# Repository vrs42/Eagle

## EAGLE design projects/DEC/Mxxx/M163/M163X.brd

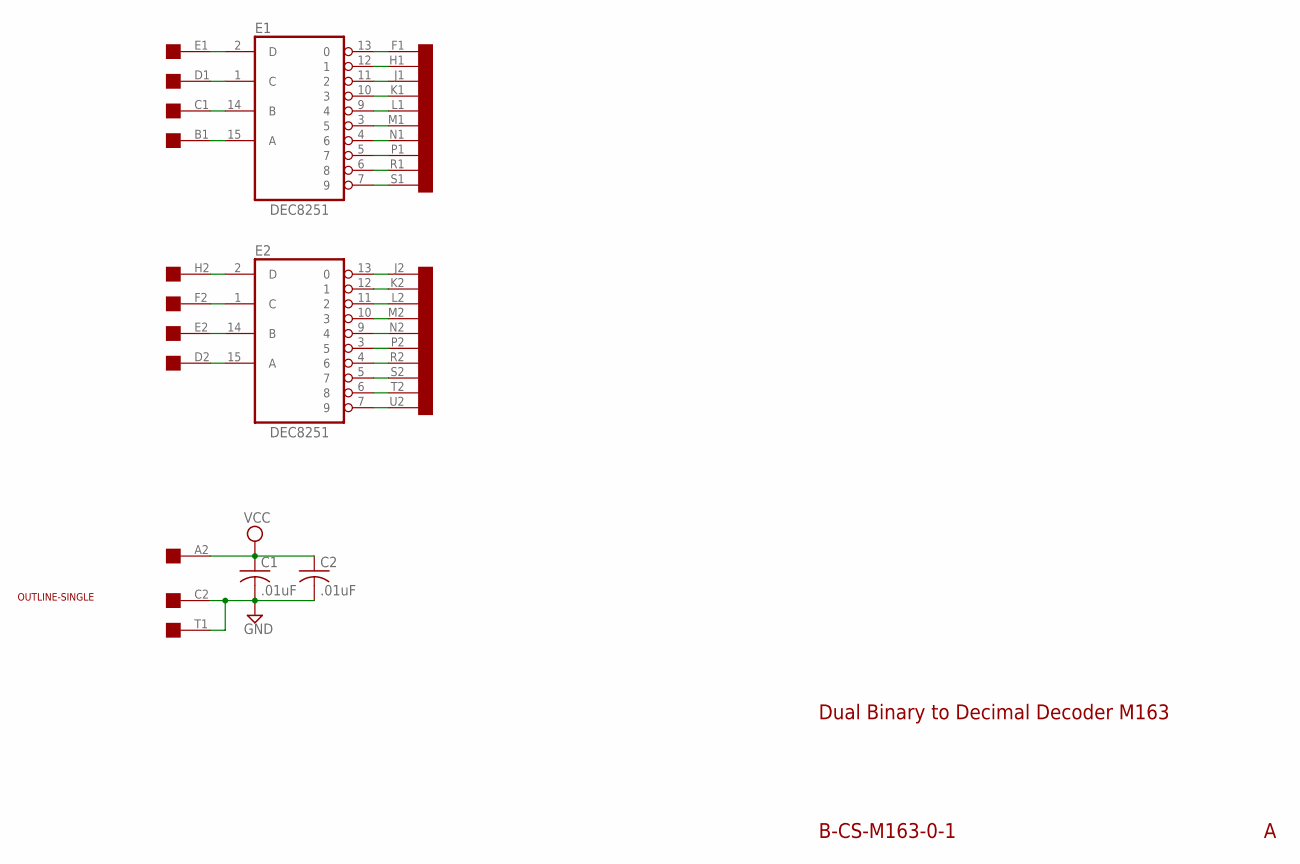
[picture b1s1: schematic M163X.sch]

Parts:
C1, C2: .01uF; C050-025X075
E1, E2: DEC8251; DIL16
U$1: OUTLINE-SINGLE; SINGLE
U$2: SINGLE; EDGE-CON2

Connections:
GND: C1.2, C2.2, E1.8 (GND), E2.8 (GND), U$2.C2, U$2.T1
unnamed: E1.15 (A), U$2.B1
unnamed: E1.14 (B), U$2.C1
unnamed: E1.1 (C), U$2.D1
unnamed: E1.2 (D), U$2.E1
unnamed: E1.13 (0), U$2.F1
unnamed: E1.12 (1), U$2.H1
unnamed: E1.11 (2), U$2.J1
unnamed: E1.10 (3), U$2.K1
unnamed: E1.3 (5), U$2.M1
unnamed: E1.9 (4), U$2.L1
unnamed: E1.4 (6), U$2.N1
unnamed: E1.5 (7), U$2.P1
unnamed: E1.6 (8), U$2.R1
unnamed: E1.7 (9), U$2.S1
unnamed: E2.2 (D), U$2.H2
unnamed: E2.1 (C), U$2.F2
unnamed: E2.15 (A), U$2.D2
unnamed: E2.14 (B), U$2.E2
unnamed: E2.11 (2), U$2.L2
unnamed: E2.10 (3), U$2.M2
unnamed: E2.9 (4), U$2.N2
unnamed: E2.3 (5), U$2.P2
unnamed: E2.4 (6), U$2.R2
unnamed: E2.5 (7), U$2.S2
unnamed: E2.6 (8), U$2.T2
unnamed: E2.12 (1), U$2.K2
unnamed: E2.13 (0), U$2.J2
unnamed: E2.7 (9), U$2.U2
VCC: C1.1, C2.1, E1.16 (VCC), E2.16 (VCC), U$2.A2

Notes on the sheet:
B-CS-M163-0-1
Dual Binary to Decimal Decoder M163

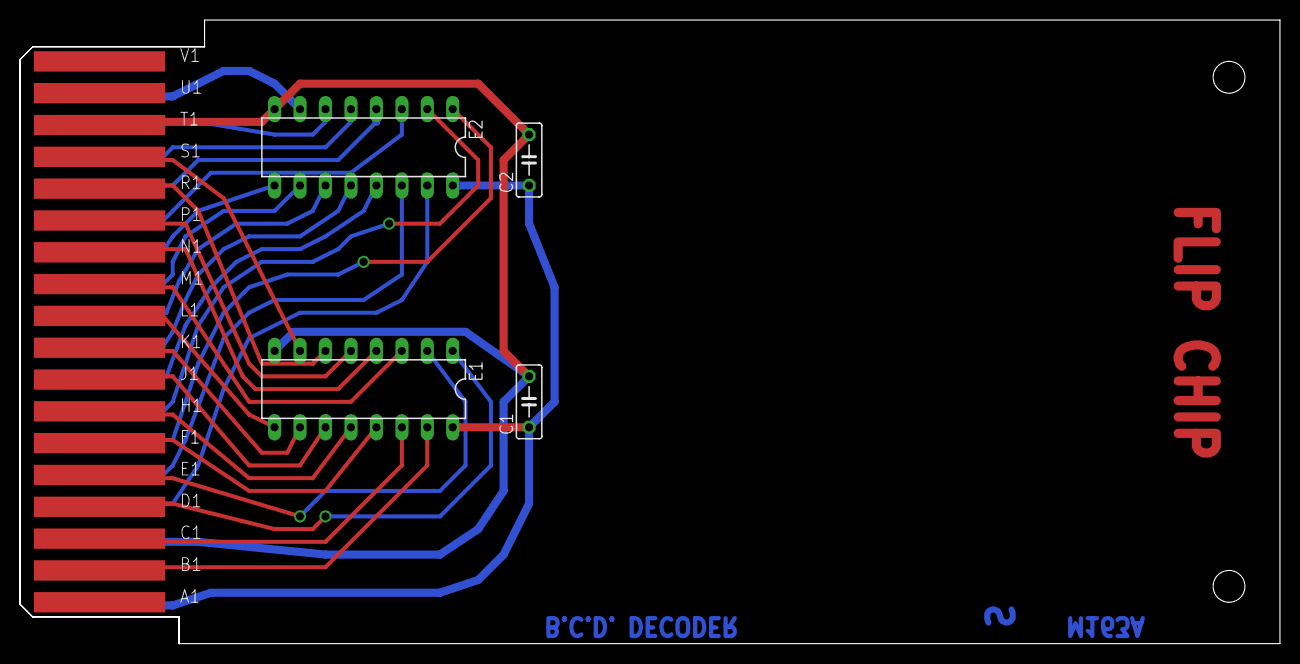
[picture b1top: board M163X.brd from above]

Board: 2 copper layers, 125.7 x 62.2 mm, 6 parts (0 on the bottom side), 30 nets.

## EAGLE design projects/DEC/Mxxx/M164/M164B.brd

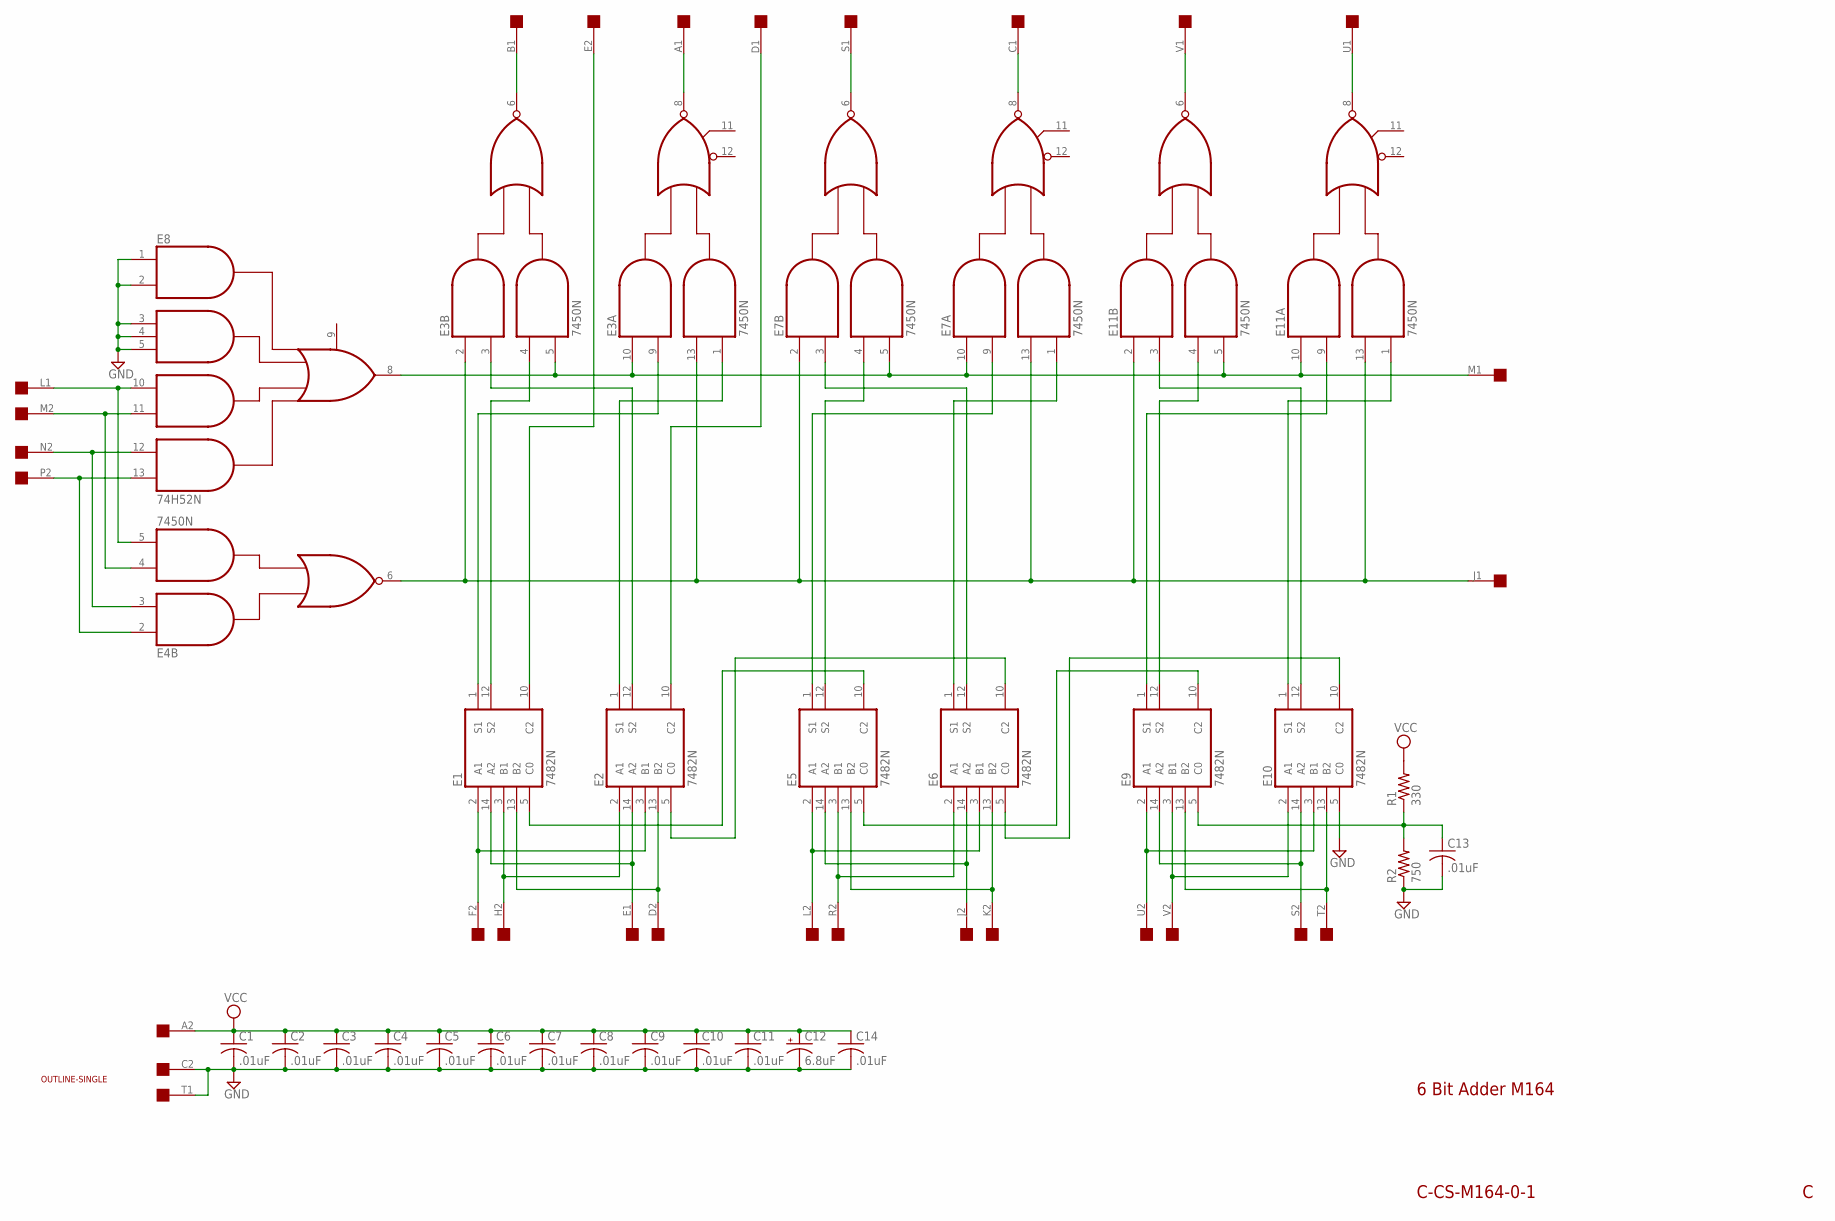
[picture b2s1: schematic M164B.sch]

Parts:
C1, C2, C3, C4, C5, C6, C7, C8, C9, C10, C11, C13, C14: .01uF; C050-025X075
C12: 6.8uF; E12-8
E1, E2, E5, E6, E9, E10: 7482N; DIL14
E3, E4, E7, E11: 7450N; DIL14
E8: 74H52N; DIL14
R1: 330; 0207/10
R2: 750; 0207/10
U$1: SINGLE; EDGE-CON2
U$2: OUTLINE-SINGLE; SINGLE

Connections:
GND: C1.2, C2.2, C3.2, C4.2, C5.2, C6.2, C7.2, C8.2, C9.2, C10.2, C11.2, C12.-, C13.2, C14.2, E1.11 (GND), E2.11 (GND), E3.7 (GND), E4.7 (GND), E5.11 (GND), E6.11 (GND), E7.7 (GND), E8.1 (I1), E8.2 (I2), E8.3 (I3), E8.4 (I4), E8.5 (I5), E8.7 (GND), E9.11 (GND), E10.5 (C0), E10.11 (GND), E11.7 (GND), R2.1, U$1.C2, U$1.T1
unnamed: E4.3 (I2), E8.12 (I12), U$1.N2
unnamed: E4.5 (I4), E8.10 (I10), U$1.L1
unnamed: E4.4 (I3), E8.11 (I11), U$1.M2
unnamed: E4.2 (I1), E8.13 (I13), U$1.P2
unnamed: E1.2 (A1), E2.3 (B1), U$1.F2
unnamed: E1.3 (B1), E2.2 (A1), U$1.H2
unnamed: E1.13 (B2), E2.13 (B2), U$1.D2
unnamed: E1.14 (A2), E2.14 (A2), U$1.E1
unnamed: E3.2 (I1), E3.13 (I3), E4.6 (O), E7.2 (I1), E7.13 (I3), E11.2 (I1), E11.13 (I3), U$1.J1
unnamed: E3.5 (I4), E3.10 (I1), E7.5 (I4), E7.10 (I1), E8.8 (O8), E11.5 (I4), E11.10 (I1), U$1.M1
unnamed: E2.12 (S2), E3.3 (I2)
unnamed: E1.12 (S2), E3.4 (I3)
unnamed: E2.1 (S1), E3.1 (I4)
unnamed: E1.1 (S1), E3.9 (I2)
unnamed: E1.10 (C2), U$1.E2
unnamed: E2.10 (C2), U$1.D1
unnamed: E3.8 (O), U$1.A1
unnamed: E3.6 (O), U$1.B1
unnamed: E1.5 (C0), E5.10 (C2)
unnamed: E2.5 (C0), E6.10 (C2)
unnamed: E5.2 (A1), E6.3 (B1), U$1.L2
unnamed: E5.3 (B1), E6.2 (A1), U$1.R2
unnamed: E5.13 (B2), E6.13 (B2), U$1.K2
unnamed: E5.14 (A2), E6.14 (A2), U$1.J2
unnamed: C13.1, E9.5 (C0), R1.1, R2.2
unnamed: E9.3 (B1), E10.2 (A1), U$1.V2
unnamed: E6.12 (S2), E7.3 (I2)
unnamed: E5.12 (S2), E7.4 (I3)
unnamed: E6.1 (S1), E7.1 (I4)
unnamed: E5.1 (S1), E7.9 (I2)
unnamed: E7.8 (O), U$1.C1
unnamed: E7.6 (O), U$1.S1
unnamed: E6.5 (C0), E10.10 (C2)
unnamed: E9.2 (A1), E10.3 (B1), U$1.U2
unnamed: E9.13 (B2), E10.13 (B2), U$1.T2
unnamed: E9.14 (A2), E10.14 (A2), U$1.S2
unnamed: E10.12 (S2), E11.3 (I2)
unnamed: E9.12 (S2), E11.4 (I3)
unnamed: E10.1 (S1), E11.1 (I4)
unnamed: E9.1 (S1), E11.9 (I2)
unnamed: E5.5 (C0), E9.10 (C2)
unnamed: E11.8 (O), U$1.U1
unnamed: E11.6 (O), U$1.V1
VCC: C1.1, C2.1, C3.1, C4.1, C5.1, C6.1, C7.1, C8.1, C9.1, C10.1, C11.1, C12.+, C14.1, E1.4 (VCC), E2.4 (VCC), E3.14 (VCC), E4.14 (VCC), E5.4 (VCC), E6.4 (VCC), E7.14 (VCC), E8.14 (VCC), E9.4 (VCC), E10.4 (VCC), E11.14 (VCC), R1.2, U$1.A2

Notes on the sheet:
6 Bit Adder M164
C-CS-M164-0-1

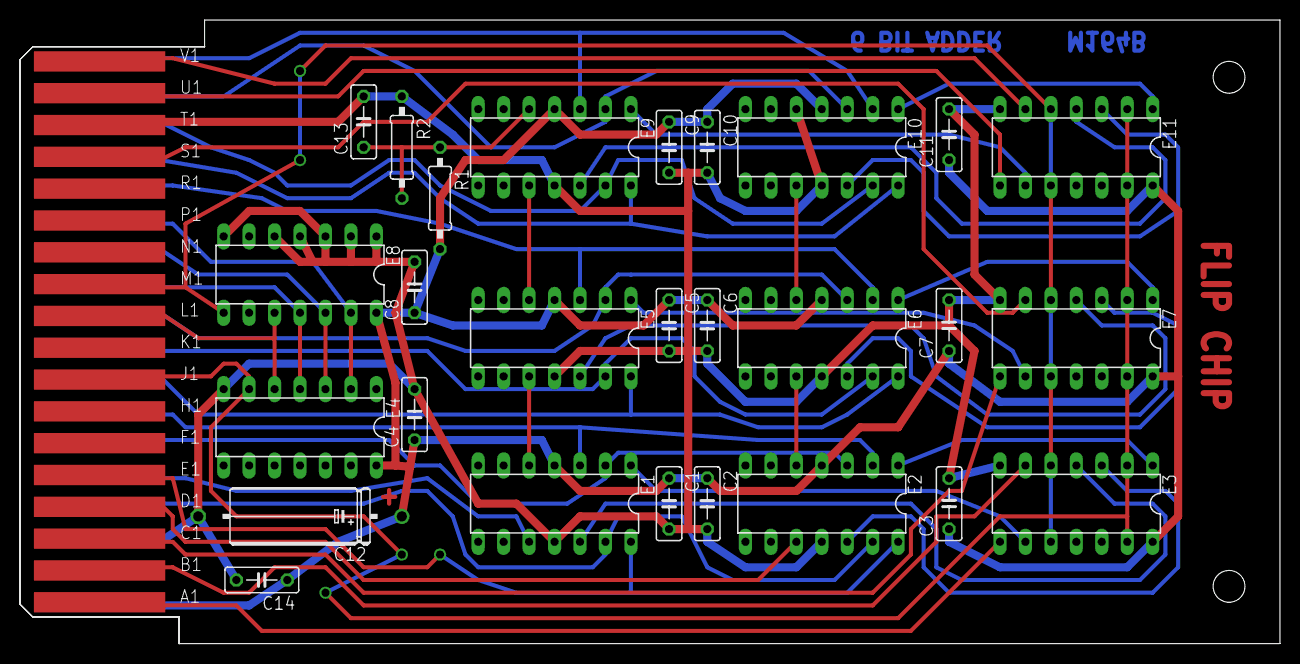
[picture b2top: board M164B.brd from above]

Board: 2 copper layers, 125.7 x 62.2 mm, 29 parts (0 on the bottom side), 45 nets.

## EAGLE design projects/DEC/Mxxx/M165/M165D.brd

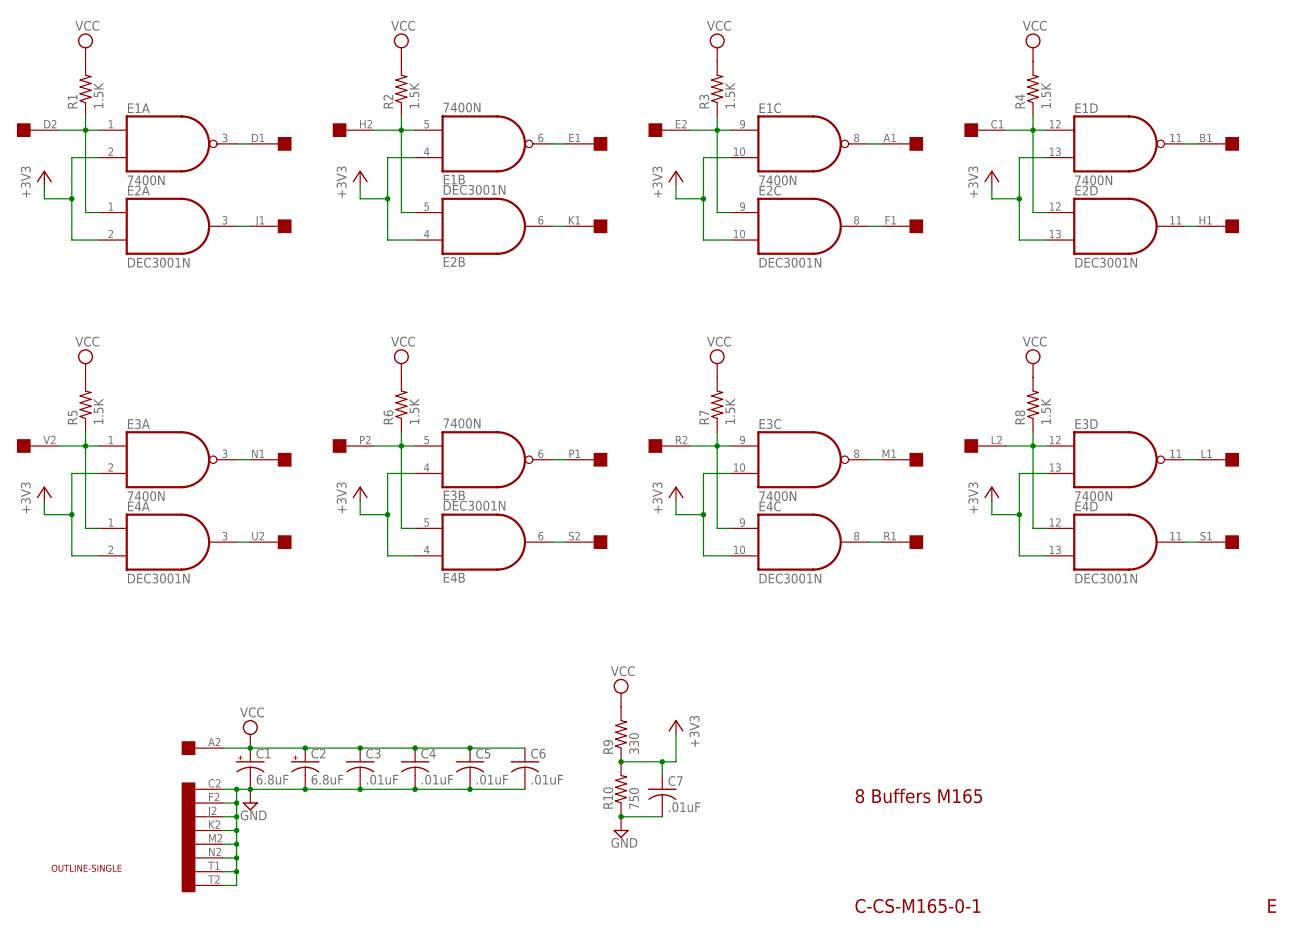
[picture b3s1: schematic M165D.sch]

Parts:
C1, C2: 6.8uF; E25-9
C3, C4, C5, C6, C7: .01uF; C050-025X075
E1, E3: 7400N; DIL14
E2, E4: DEC3001N; DIL14
R1, R2, R3, R4, R5, R6, R7, R8: 1.5K; 0207/10
R9: 330; 0207/10
R10: 750; 0207/10
U$1: SINGLE; EDGE-CON2
U$2: OUTLINE-SINGLE; SINGLE

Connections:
+3V3: C7.1, E1.2 (I1), E1.4 (I0), E1.10 (I1), E1.13 (I1), E2.2 (I1), E2.4 (I0), E2.10 (I1), E2.13 (I1), E3.2 (I1), E3.4 (I0), E3.10 (I1), E3.13 (I1), E4.2 (I1), E4.4 (I0), E4.10 (I1), E4.13 (I1), R9.1, R10.2
GND: C1.-, C2.-, C3.2, C4.2, C5.2, C6.2, C7.2, E1.7 (GND), E2.7 (GND), E3.7 (GND), E4.7 (GND), R10.1, U$1.C2, U$1.F2, U$1.J2, U$1.K2, U$1.M2, U$1.N2, U$1.T1, U$1.T2
unnamed: E1.1 (I0), E2.1 (I0), R1.1, U$1.D2
unnamed: E1.5 (I1), E2.5 (I1), R2.1, U$1.H2
unnamed: E2.3 (O), U$1.J1
unnamed: E1.3 (O), U$1.D1
unnamed: E2.6 (O), U$1.K1
unnamed: E1.6 (O), U$1.E1
unnamed: E1.9 (I0), E2.9 (I0), R3.1, U$1.E2
unnamed: E2.8 (O), U$1.F1
unnamed: E1.8 (O), U$1.A1
unnamed: E1.12 (I0), E2.12 (I0), R4.1, U$1.C1
unnamed: E2.11 (O), U$1.H1
unnamed: E1.11 (O), U$1.B1
unnamed: E3.1 (I0), E4.1 (I0), R5.1, U$1.V2
unnamed: E4.3 (O), U$1.U2
unnamed: E3.3 (O), U$1.N1
unnamed: E3.5 (I1), E4.5 (I1), R6.1, U$1.P2
unnamed: E4.6 (O), U$1.S2
unnamed: E3.6 (O), U$1.P1
unnamed: E3.9 (I0), E4.9 (I0), R7.1, U$1.R2
unnamed: E4.8 (O), U$1.R1
unnamed: E3.8 (O), U$1.M1
unnamed: E3.12 (I0), E4.12 (I0), R8.1, U$1.L2
unnamed: E4.11 (O), U$1.S1
unnamed: E3.11 (O), U$1.L1
VCC: C1.+, C2.+, C3.1, C4.1, C5.1, C6.1, E1.14 (VCC), E2.14 (VCC), E3.14 (VCC), E4.14 (VCC), R1.2, R2.2, R3.2, R4.2, R5.2, R6.2, R7.2, R8.2, R9.2, U$1.A2

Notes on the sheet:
8 Buffers M165
C-CS-M165-0-1

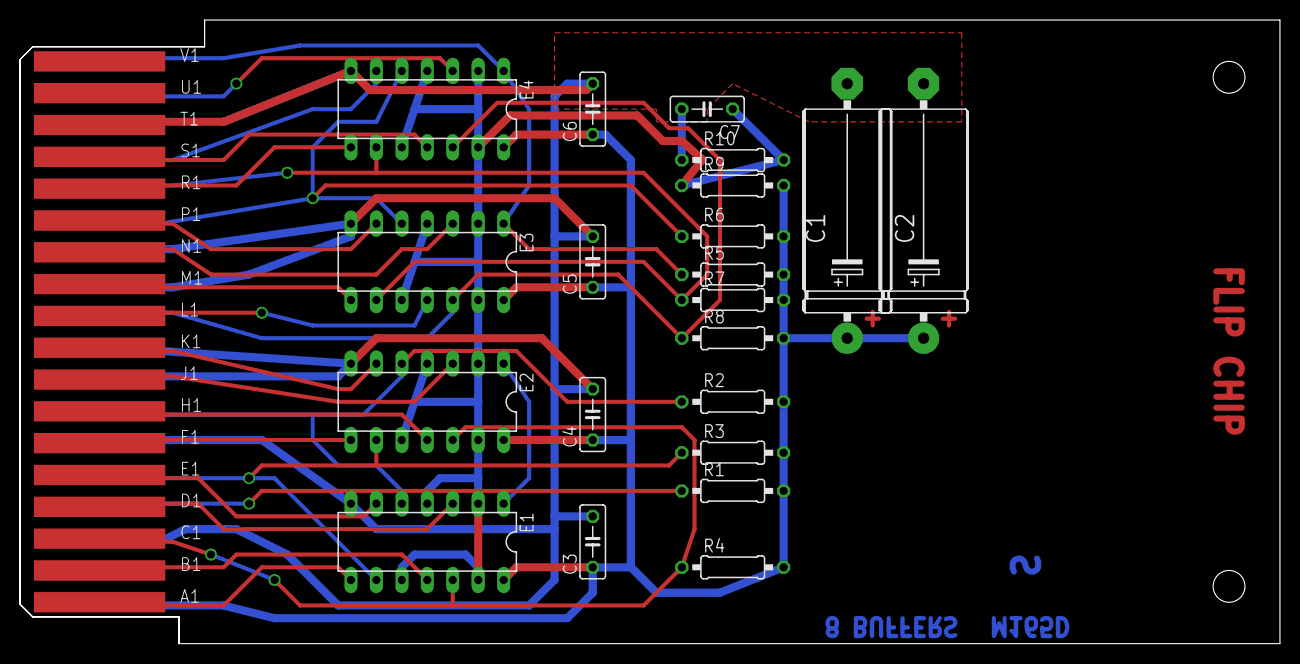
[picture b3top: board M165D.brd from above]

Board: 2 copper layers, 125.7 x 62.2 mm, 23 parts (0 on the bottom side), 27 nets.

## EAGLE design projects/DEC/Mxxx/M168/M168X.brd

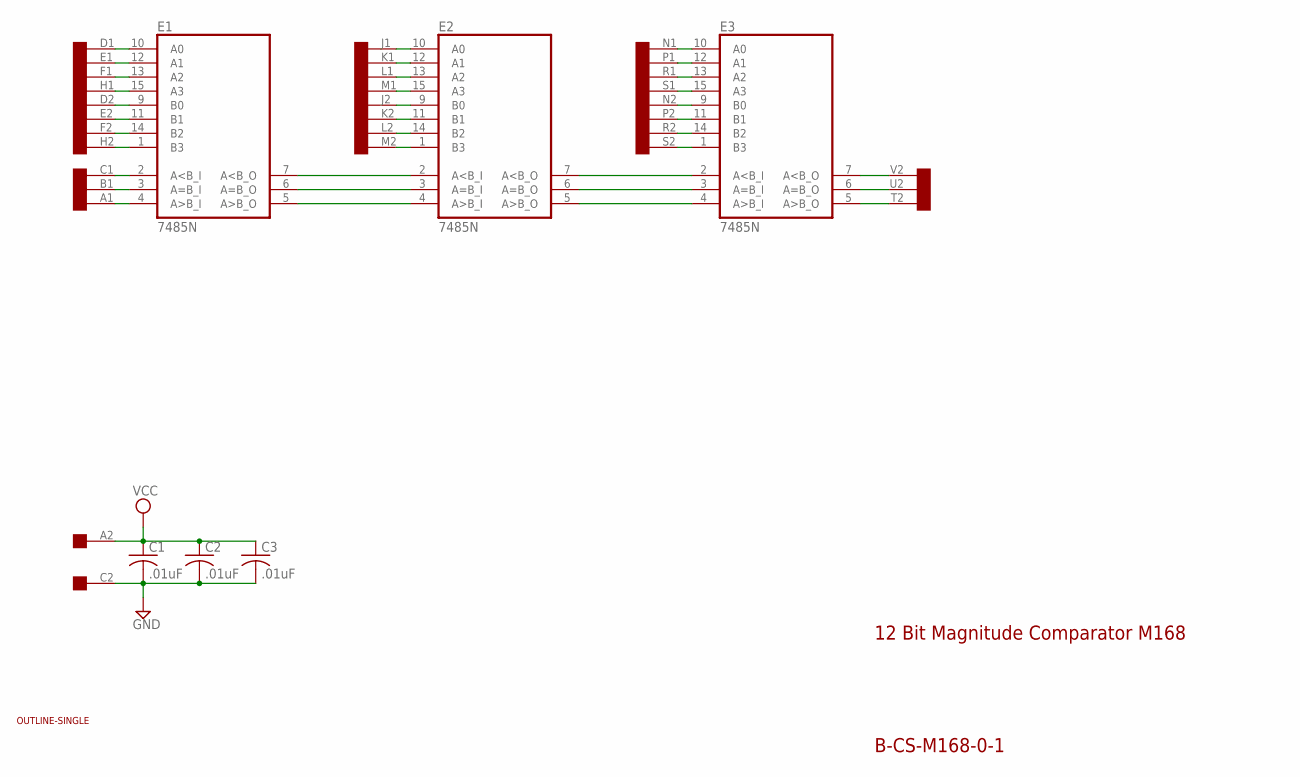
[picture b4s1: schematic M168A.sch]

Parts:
C1, C2, C3: .01uF; C050-025X075
E1, E2, E3: 7485N; DIL16
U$1: SINGLE; EDGE-CON2
U$2: OUTLINE-SINGLE; SINGLE

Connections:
A1: E1.4 (A>B_I), U$1.A1
B1: E1.3 (A=B_I), U$1.B1
C1: E1.2 (A<B_I), U$1.C1
D1: E1.10 (A0), U$1.D1
D2: E1.9 (B0), U$1.D2
E1: E1.12 (A1), U$1.E1
E2: E1.11 (B1), U$1.E2
F1: E1.13 (A2), U$1.F1
F2: E1.14 (B2), U$1.F2
GND: C1.2, C2.2, C3.2, E1.8 (GND), E2.8 (GND), E3.8 (GND), U$1.C2
H1: E1.15 (A3), U$1.H1
H2: E1.1 (B3), U$1.H2
J1: E2.10 (A0), U$1.J1
J2: E2.9 (B0), U$1.J2
K1: E2.12 (A1), U$1.K1
K2: E2.11 (B1), U$1.K2
L1: E2.13 (A2), U$1.L1
L2: E2.14 (B2), U$1.L2
M1: E2.15 (A3), U$1.M1
M2: E2.1 (B3), U$1.M2
N1: E3.10 (A0), U$1.N1
N2: E3.9 (B0), U$1.N2
unnamed: E1.6 (A=B_O), E2.3 (A=B_I)
unnamed: E1.7 (A<B_O), E2.2 (A<B_I)
unnamed: E1.5 (A>B_O), E2.4 (A>B_I)
unnamed: E2.6 (A=B_O), E3.3 (A=B_I)
unnamed: E2.7 (A<B_O), E3.2 (A<B_I)
unnamed: E2.5 (A>B_O), E3.4 (A>B_I)
P1: E3.12 (A1), U$1.P1
P2: E3.11 (B1), U$1.P2
R1: E3.13 (A2), U$1.R1
R2: E3.14 (B2), U$1.R2
S1: E3.15 (A3), U$1.S1
S2: E3.1 (B3), U$1.S2
T2: E3.5 (A>B_O), U$1.T2
U2: E3.6 (A=B_O), U$1.U2
V2: E3.7 (A<B_O), U$1.V2
VCC: C1.1, C2.1, C3.1, E1.16 (VCC), E2.16 (VCC), E3.16 (VCC), U$1.A2

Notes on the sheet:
12 Bit Magnitude Comparator M168
B-CS-M168-0-1

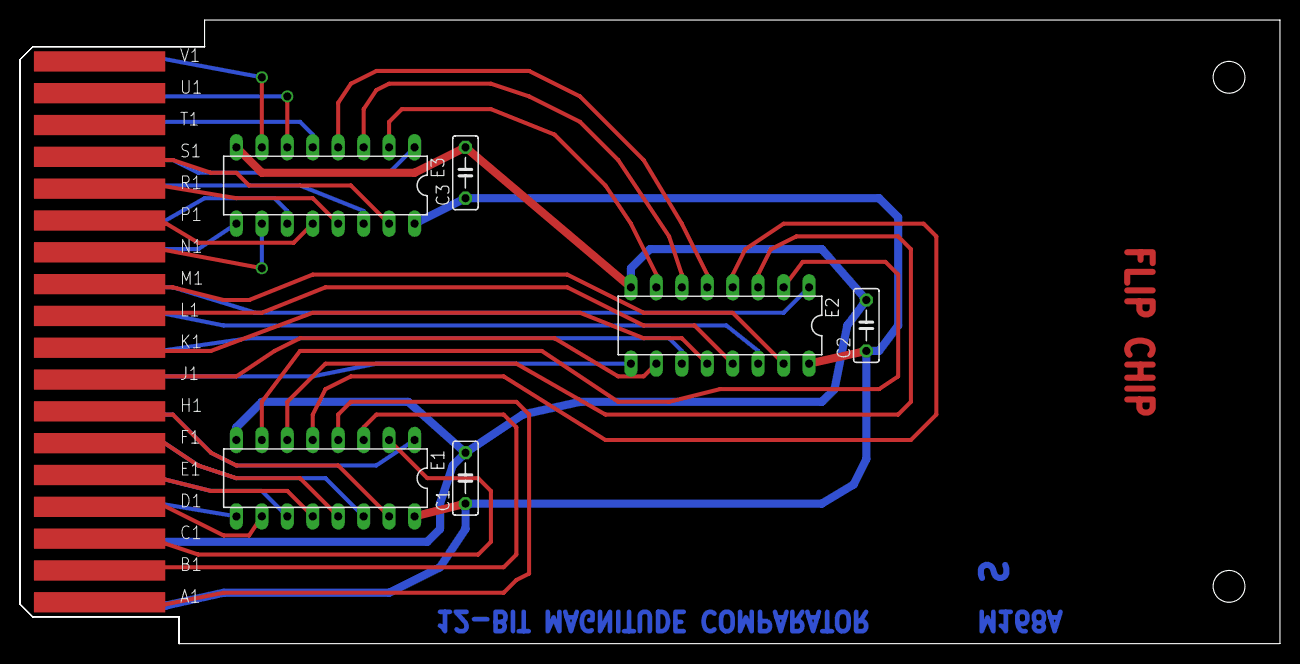
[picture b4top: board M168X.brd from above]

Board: 2 copper layers, 125.7 x 62.2 mm, 8 parts (0 on the bottom side), 38 nets.

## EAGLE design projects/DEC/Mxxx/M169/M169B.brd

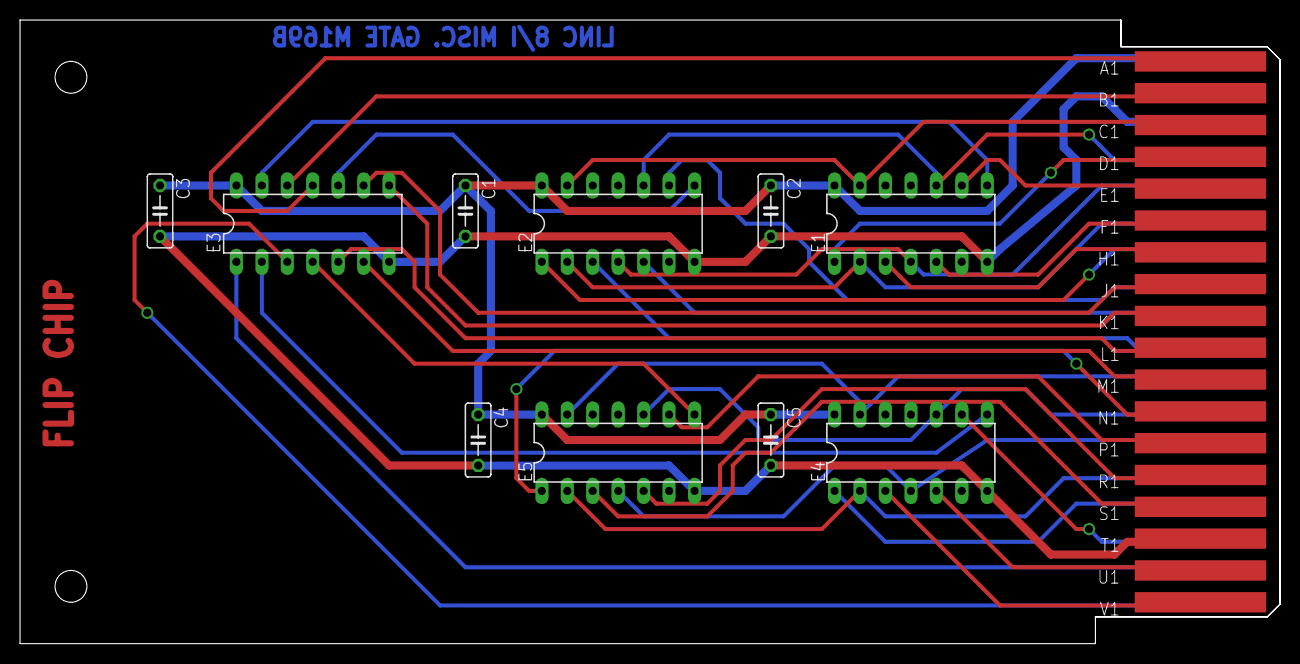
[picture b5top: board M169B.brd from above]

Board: 2 copper layers, 125.7 x 62.2 mm, 13 parts (0 on the bottom side), 38 nets.

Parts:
C1, C2, C3, C4, C5: .01uf; C050-025X075
E1, E2, E4, E5: 7453N; DIL14
E3: 7400N; DIL14
U$1: OUTLINE-SINGLE; SINGLE
U$2: EDGE-CON2
U$3: FLIPCHIP

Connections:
GND: C1.2, C2.2, C3.2, C4.2, C5.2, E1.7, E2.7, E3.7, E4.7, E5.7, U$2.C2, U$2.T1
unnamed: E1.8, E3.13
unnamed: E3.11, U$2.A1
unnamed: E1.13, E2.13, U$2.C1
unnamed: E1.10, E2.10, U$2.D2
unnamed: E1.4, E2.4, U$2.E2
unnamed: E1.2, E2.2, U$2.F2
unnamed: E2.8, E3.10
unnamed: E3.8, U$2.K1
unnamed: E2.9, U$2.J2
unnamed: E1.5, U$2.F1
unnamed: E1.1, U$2.D1
unnamed: E1.3, U$2.H1
unnamed: E1.9, U$2.E1
unnamed: E3.12, U$2.B1
unnamed: E2.5, U$2.K2
unnamed: E2.1, U$2.H2
unnamed: E2.3, U$2.L2
unnamed: E4.13, E5.13, U$2.M2
unnamed: E4.10, E5.10, U$2.N2
unnamed: E4.4, E5.4, U$2.P2
unnamed: E4.2, E5.2, U$2.R2
unnamed: E3.4, E5.8
unnamed: E3.2, E4.8
unnamed: E3.9, U$2.J1
unnamed: E4.9, U$2.T2
unnamed: E5.1, U$2.N1
unnamed: E5.5, U$2.R1
unnamed: E5.3, U$2.S1
unnamed: E5.9, U$2.P1
unnamed: E3.5, U$2.L1
unnamed: E4.5, U$2.U1
unnamed: E4.1, U$2.S2
unnamed: E4.3, U$2.V1
unnamed: E3.1, U$2.U2
unnamed: E3.6, U$2.M1
unnamed: E3.3, U$2.V2
VCC: C1.1, C2.1, C3.1, C4.1, C5.1, E1.14, E2.14, E3.14, E4.14, E5.14, U$2.A2

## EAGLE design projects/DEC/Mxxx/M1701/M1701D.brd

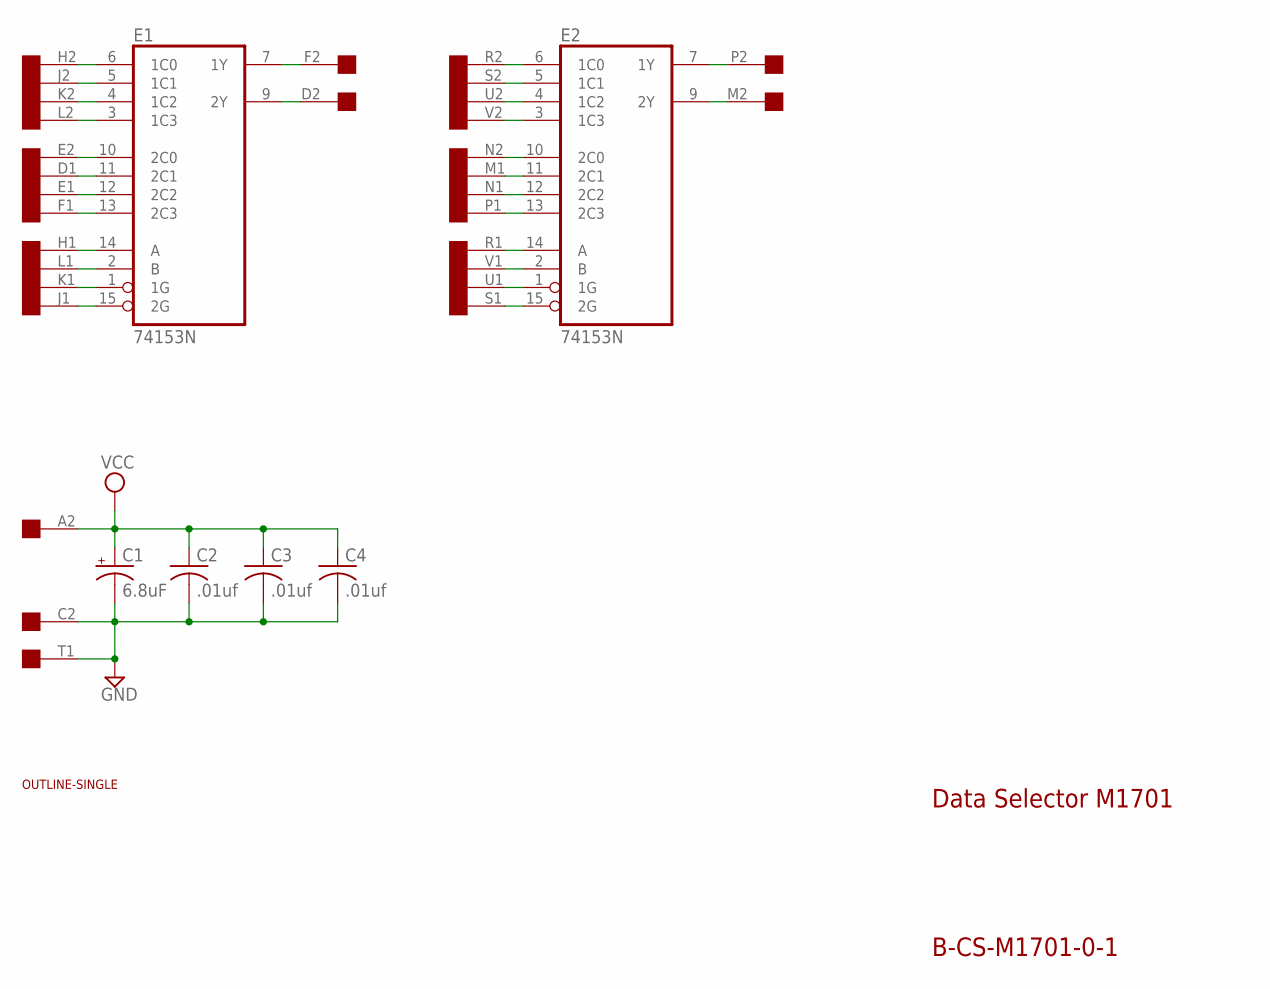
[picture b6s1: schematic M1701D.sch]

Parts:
C1: 6.8uF; E12-8
C2, C3, C4: .01uf; C050-025X075
E1, E2: 74153N; DIL16
U$1: OUTLINE-SINGLE; SINGLE
U$2: SINGLE; EDGE-CON2

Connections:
GND: C1.-, C2.2, C3.2, C4.2, E1.8 (GND), E2.8 (GND), U$2.C2, U$2.T1
unnamed: E1.6 (1C0), U$2.H2
unnamed: E1.5 (1C1), U$2.J2
unnamed: E1.4 (1C2), U$2.K2
unnamed: E1.3 (1C3), U$2.L2
unnamed: E1.10 (2C0), U$2.E2
unnamed: E1.11 (2C1), U$2.D1
unnamed: E1.12 (2C2), U$2.E1
unnamed: E1.13 (2C3), U$2.F1
unnamed: E1.1 (1G), U$2.K1
unnamed: E1.2 (B), U$2.L1
unnamed: E1.14 (A), U$2.H1
unnamed: E1.15 (2G), U$2.J1
unnamed: E1.9 (2Y), U$2.D2
unnamed: E1.7 (1Y), U$2.F2
unnamed: E2.6 (1C0), U$2.R2
unnamed: E2.5 (1C1), U$2.S2
unnamed: E2.4 (1C2), U$2.U2
unnamed: E2.3 (1C3), U$2.V2
unnamed: E2.1 (1G), U$2.U1
unnamed: E2.15 (2G), U$2.S1
unnamed: E2.2 (B), U$2.V1
unnamed: E2.10 (2C0), U$2.N2
unnamed: E2.11 (2C1), U$2.M1
unnamed: E2.12 (2C2), U$2.N1
unnamed: E2.13 (2C3), U$2.P1
unnamed: E2.14 (A), U$2.R1
unnamed: E2.7 (1Y), U$2.P2
unnamed: E2.9 (2Y), U$2.M2
VCC: C1.+, C2.1, C3.1, C4.1, E1.16 (VCC), E2.16 (VCC), U$2.A2

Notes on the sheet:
Data Selector M1701
B-CS-M1701-0-1

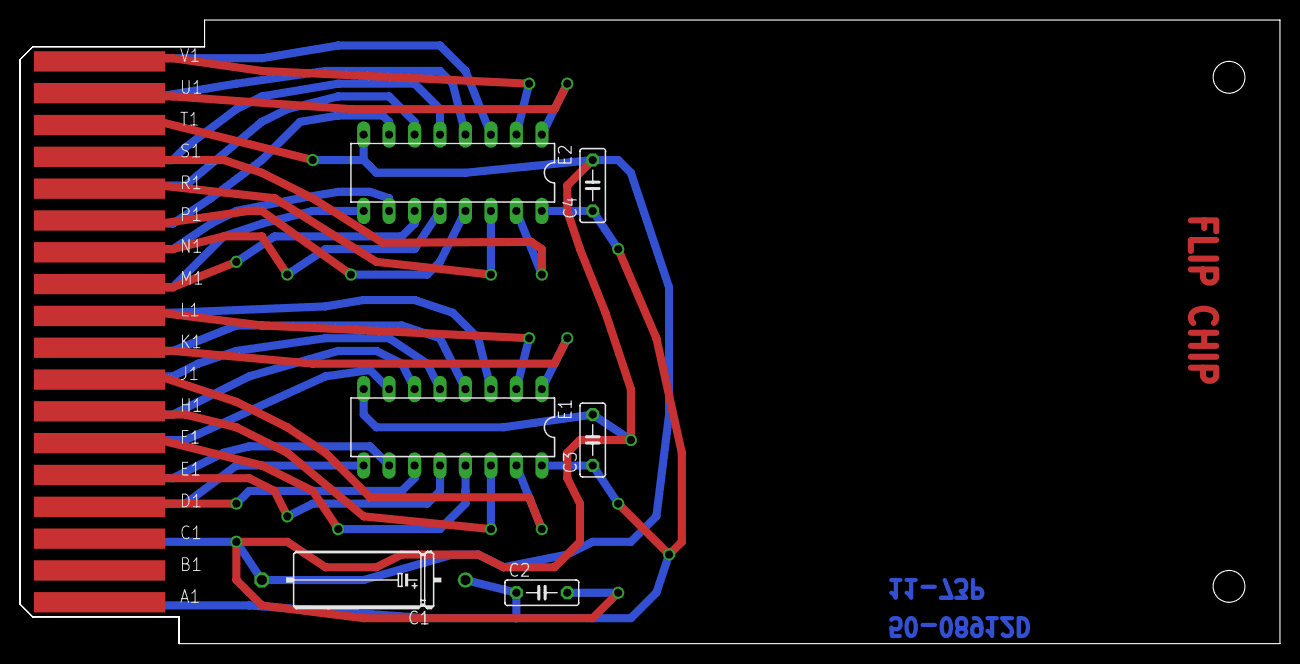
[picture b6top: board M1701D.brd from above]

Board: 2 copper layers, 125.7 x 62.2 mm, 8 parts (0 on the bottom side), 30 nets.

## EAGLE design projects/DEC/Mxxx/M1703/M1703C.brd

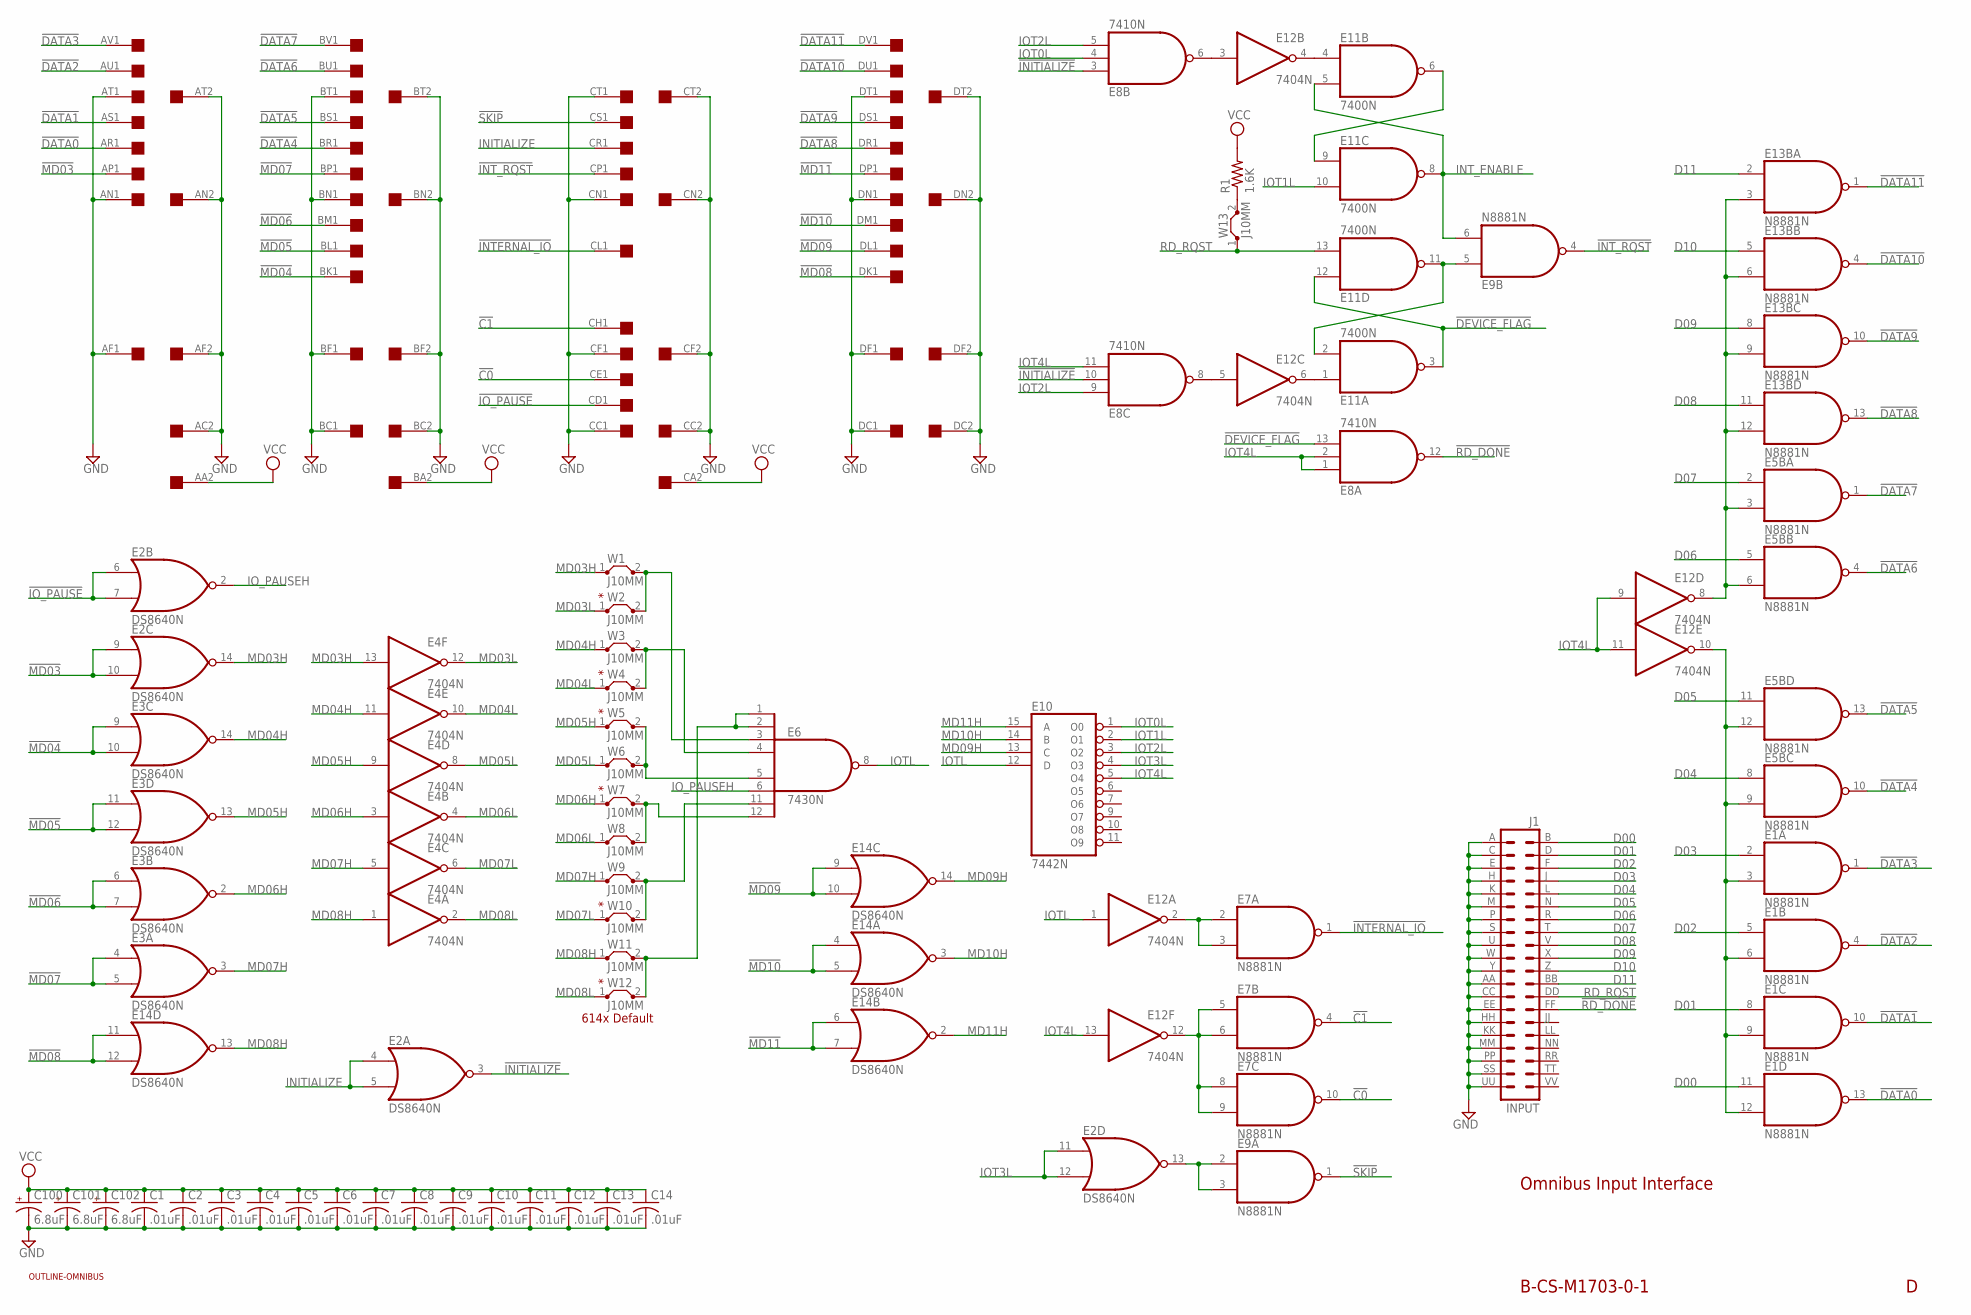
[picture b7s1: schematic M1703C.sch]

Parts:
C1, C2, C3, C4, C5, C6, C7, C8, C9, C10, C11, C12, C13, C14: .01uF; C075-032X103
C100, C101, C102: 6.8uF; E12-8
E1, E5B, E7, E9, E13B: N8881N; DIL14
E2, E3, E14: DS8640N; DIL14
E4, E12: 7404N; DIL14
E6: 7430N; DIL14
E8: 7410N; DIL14
E10: 7442N; DIL16
E11: 7400N; DIL14
J1: INPUT; DEC40PINH
R1: 1.6K; 0207/10
U$2: QUAD; EDGE-CON8
U$4: OUTLINE-OMNIBUS; OMNIBUS
W1, W2, W3, W4, W5, W6, W7, W8, W9, W10, W11, W12, W13: J10MM; 10

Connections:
!C0: E7.10 (O), U$2.CE1
!C1: E7.4 (O), U$2.CH1
!DATA0: E1.13 (O), U$2.AR1
!DATA1: E1.10 (O), U$2.AS1
!DATA2: E1.4 (O), U$2.AU1
!DATA3: E1.1 (O), U$2.AV1
!DATA4: E5B.10 (O), U$2.BR1
!DATA5: E5B.13 (O), U$2.BS1
!DATA6: E5B.4 (O), U$2.BU1
!DATA7: E5B.1 (O), U$2.BV1
!DATA8: E13B.13 (O), U$2.DR1
!DATA9: E13B.10 (O), U$2.DS1
!DATA10: E13B.4 (O), U$2.DU1
!DATA11: E13B.1 (O), U$2.DV1
!DEVICE_FLAG: E8.13 (I2), E11.3 (O), E11.12 (I0)
!INITIALIZE: E2.3 (O), E8.3 (I0), E8.10 (I1)
!INTERNAL_IO: E7.1 (O), U$2.CL1
!INT_ENABLE: E11.6 (O), E11.9 (I0)
!INT_RQST: E9.4 (O), U$2.CP1
!IO_PAUSE: E2.6 (I0), E2.7 (I1), U$2.CD1
!MD03: E2.9 (I0), E2.10 (I1), U$2.AP1
!MD04: E3.9 (I0), E3.10 (I1), U$2.BK1
!MD05: E3.11 (I0), E3.12 (I1), U$2.BL1
!MD06: E3.6 (I0), E3.7 (I1), U$2.BM1
!MD07: E3.4 (I0), E3.5 (I1), U$2.BP1
!MD08: E14.11 (I0), E14.12 (I1), U$2.DK1
!MD09: E14.9 (I0), E14.10 (I1), U$2.DL1
!MD10: E14.4 (I0), E14.5 (I1), U$2.DM1
!MD11: E14.6 (I0), E14.7 (I1), U$2.DP1
!RD_DONE: E8.12 (O), J1.FF (28)
!SKIP: E9.1 (O), U$2.CS1
D00: E1.11 (I0), J1.B (2)
D01: E1.8 (I0), J1.D (4)
D02: E1.5 (I0), J1.F (6)
D03: E1.2 (I0), J1.J (8)
D04: E5B.8 (I0), J1.L (10)
D05: E5B.11 (I0), J1.N (12)
D06: E5B.5 (I0), J1.R (14)
D07: E5B.2 (I0), J1.T (16)
D08: E13B.11 (I0), J1.V (18)
D09: E13B.8 (I0), J1.X (20)
D10: E13B.5 (I0), J1.Z (22)
D11: E13B.2 (I0), J1.BB (24)
DEVICE_FLAG: E9.5 (I0), E11.2 (I1), E11.11 (O)
GND: C1.2, C2.2, C3.2, C4.2, C5.2, C6.2, C7.2, C8.2, C9.2, C10.2, C11.2, C12.2, C13.2, C14.2, C100.-, C101.-, C102.-, E1.7 (GND), E2.1 (GND), E3.1 (GND), E4.7 (GND), E5B.7 (GND), E6.7 (GND), E7.7 (GND), E8.7 (GND), E9.7 (GND), E10.8 (GND), E11.7 (GND), E12.7 (GND), E13B.7 (GND), E14.1 (GND), J1.A (1), J1.AA (23), J1.C (3), J1.CC (25), J1.E (5), J1.EE (27), J1.H (7), J1.HH (29), J1.K (9), J1.KK (31), J1.M (11), J1.MM (33), J1.P (13), J1.PP (35), J1.S (15), J1.SS (37), J1.U (17), J1.UU (39), J1.W (19), J1.Y (21), U$2.AC2, U$2.AF1, U$2.AF2, U$2.AN1, U$2.AN2, U$2.AT1, U$2.AT2, U$2.BC1, U$2.BC2, U$2.BF1, U$2.BF2, U$2.BN1, U$2.BN2, U$2.BT1, U$2.BT2, U$2.CC1, U$2.CC2, U$2.CF1, U$2.CF2, U$2.CN1, U$2.CN2, U$2.CT1, U$2.CT2, U$2.DC1, U$2.DC2, U$2.DF1, U$2.DF2, U$2.DN1, U$2.DN2, U$2.DT1, U$2.DT2
INITIALIZE: E2.4 (I0), E2.5 (I1), U$2.CR1
INT_ENABLE: E9.6 (I1), E11.5 (I1), E11.8 (O)
IOT0L: E8.4 (I1), E10.1 (O0)
IOT1L: E10.2 (O1), E11.10 (I1)
IOT2L: E8.5 (I2), E8.9 (I0), E10.3 (O2)
IOT3L: E2.11 (I0), E2.12 (I1), E10.4 (O3)
IOT4L: E8.1 (I0), E8.2 (I1), E8.11 (I2), E10.5 (O4), E12.9 (I), E12.11 (I), E12.13 (I)
IOTL: E6.8 (O), E10.12 (D), E12.1 (I)
IO_PAUSEH: E2.2 (O), E6.6 (I5)
MD03H: E2.14 (O), E4.13 (I), W1.1
MD03L: E4.12 (O), W2.1
MD03OK: E6.3 (I2), W1.2, W2.2
MD04H: E3.14 (O), E4.11 (I), W3.1
MD04L: E4.10 (O), W4.1
MD04OK: E6.4 (I3), W3.2, W4.2
MD05H: E3.13 (O), E4.9 (I), W5.1
MD05L: E4.8 (O), W6.1
MD05OK: E6.5 (I4), W5.2, W6.2
MD06H: E3.2 (O), E4.3 (I), W7.1
MD06L: E4.4 (O), W8.1
MD06OK: E6.12 (I7), W7.2, W8.2
MD07H: E3.3 (O), E4.5 (I), W9.1
MD07L: E4.6 (O), W10.1
MD07OK: E6.11 (I6), W9.2, W10.2
MD08H: E4.1 (I), E14.13 (O), W11.1
MD08L: E4.2 (O), W12.1
MD08OK: E6.1 (I0), E6.2 (I1), W11.2, W12.2
MD09H: E10.13 (C), E14.14 (O)
MD10H: E10.14 (B), E14.3 (O)
MD11H: E10.15 (A), E14.2 (O)
unnamed: E1.3 (I1), E1.6 (I1), E1.9 (I1), E1.12 (I1), E5B.9 (I1), E5B.12 (I1), E12.10 (O)
unnamed: R1.1, W13.2
unnamed: E5B.3 (I1), E5B.6 (I1), E12.8 (O), E13B.3 (I1), E13B.6 (I1), E13B.9 (I1), E13B.12 (I1)
unnamed: E11.4 (I0), E12.4 (O)
unnamed: E2.13 (O), E9.2 (I0), E9.3 (I1)
unnamed: E8.6 (O), E12.3 (I)
unnamed: E11.1 (I0), E12.6 (O)
unnamed: E8.8 (O), E12.5 (I)
unnamed: E7.2 (I0), E7.3 (I1), E12.2 (O)
unnamed: E7.5 (I0), E7.6 (I1), E7.8 (I0), E7.9 (I1), E12.12 (O)
RD_RQST: E11.13 (I1), J1.DD (26), W13.1
VCC: C1.1, C2.1, C3.1, C4.1, C5.1, C6.1, C7.1, C8.1, C9.1, C10.1, C11.1, C12.1, C13.1, C14.1, C100.+, C101.+, C102.+, E1.14 (VCC), E2.8 (VCC), E3.8 (VCC), E4.14 (VCC), E5B.14 (VCC), E6.14 (VCC), E7.14 (VCC), E8.14 (VCC), E9.14 (VCC), E10.16 (VCC), E11.14 (VCC), E12.14 (VCC), E13B.14 (VCC), E14.8 (VCC), R1.2, U$2.AA2, U$2.BA2, U$2.CA2

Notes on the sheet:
B-CS-M1703-0-1
Omnibus Input Interface
614x Default
